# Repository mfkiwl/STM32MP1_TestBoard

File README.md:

### STM32MP1 Embedded Linux breakout board ###

[Bill of materials](STM32MP1_TestBoard/doc/bom/STM32MP1_TestBoard.csv)

[DataSheets](STM32MP1_TestBoard/doc/datasheets)

#### System Overview ####

#### Power Supply ####

#### MPU Power Supply ####

#### MPU DDR ####

#### MicroSD connectors ####

#### USB Connectors ####

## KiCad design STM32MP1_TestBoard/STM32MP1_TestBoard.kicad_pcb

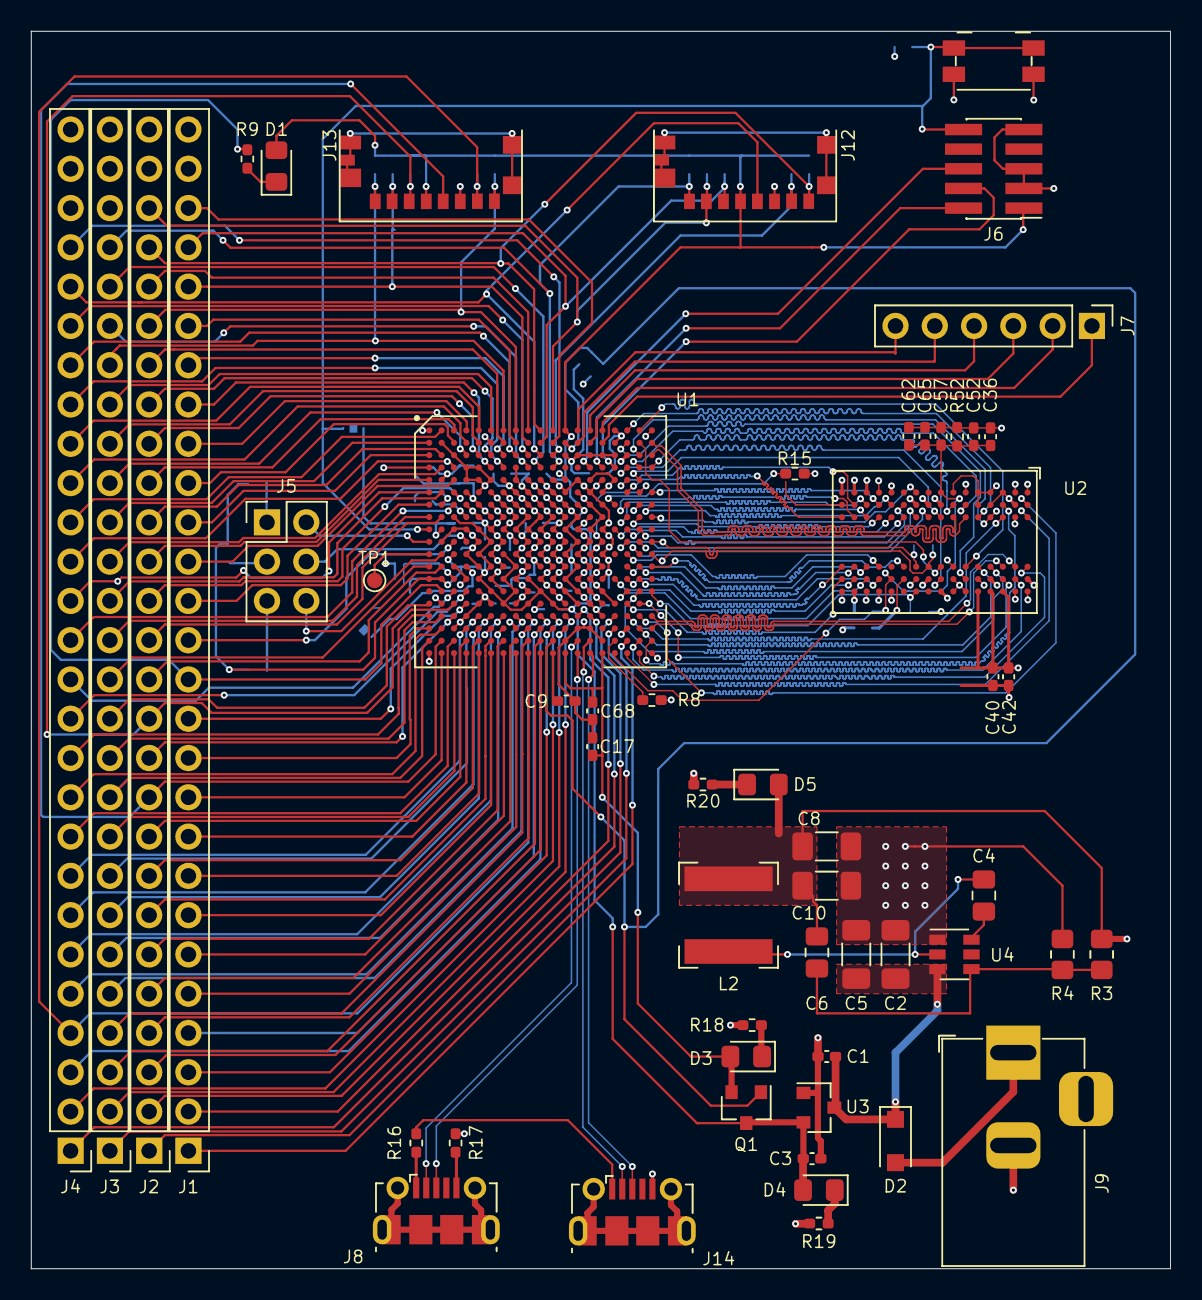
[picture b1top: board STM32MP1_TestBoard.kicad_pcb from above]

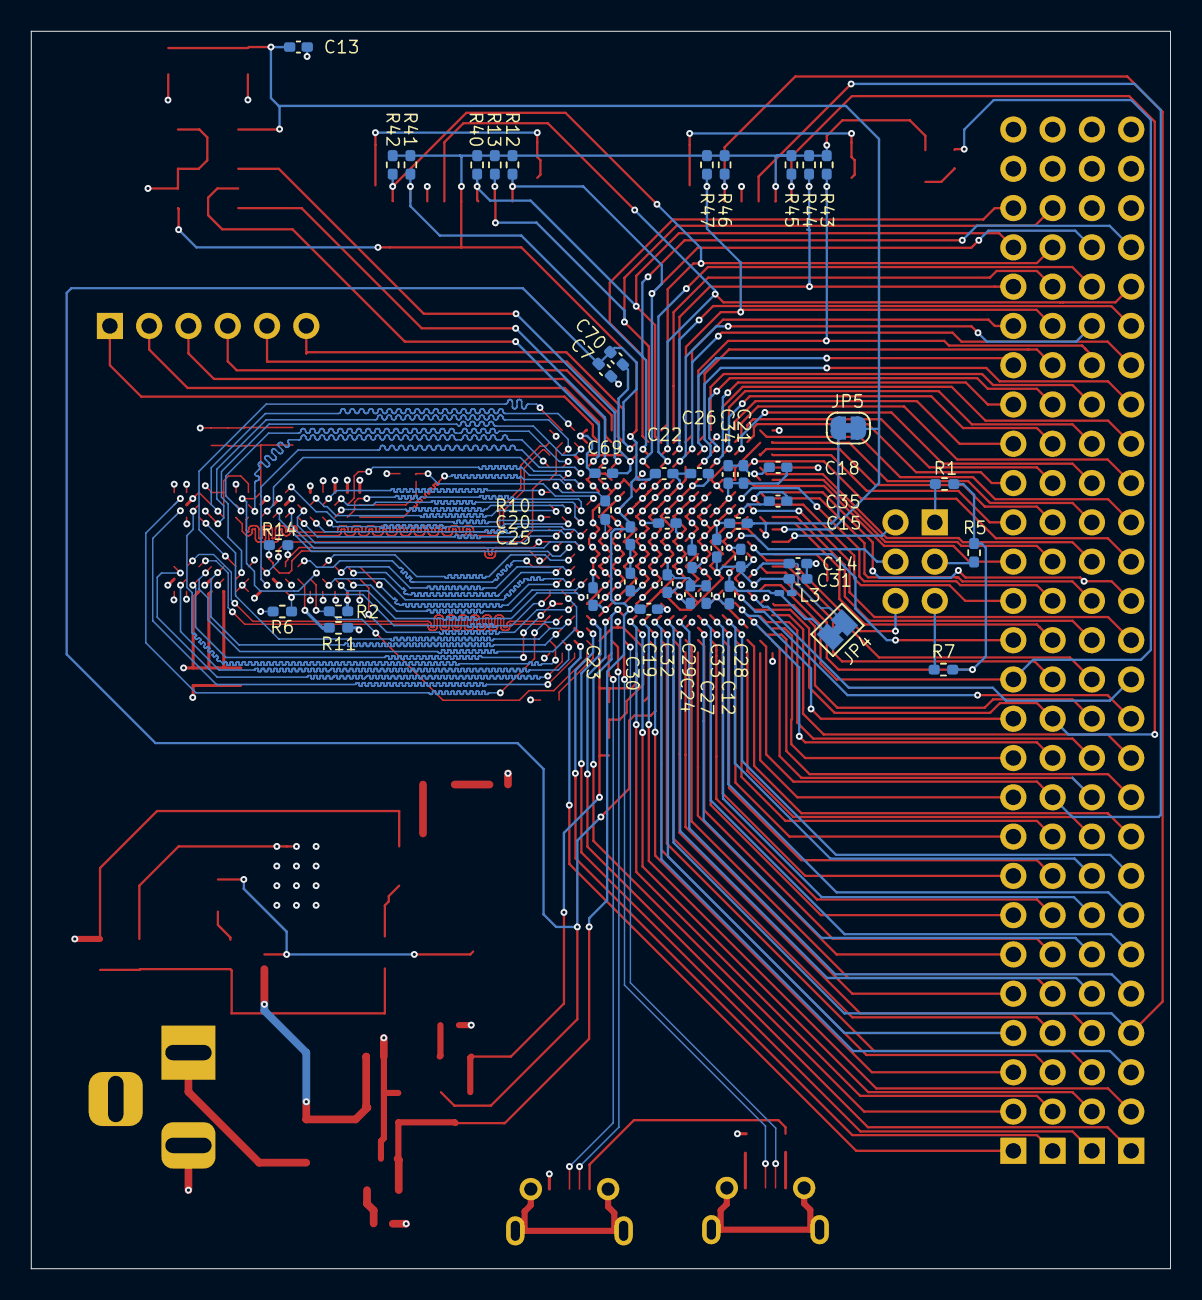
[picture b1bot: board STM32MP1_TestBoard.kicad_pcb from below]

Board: 4 copper layers, 73.7 x 80.0 mm, 100 parts (46 on the bottom side), 195 nets.

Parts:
C1, C12, C14, C17, C18, C19, C20, C21, C22, C23, C24, C25, C26, C27, C28, C29, C30, C31, C32, C33, C34, C35, C68, C70: 1uF; C_0402_1005Metric_Pad0.74x0.62mm_HandSolder
C2, C5, C8, C10: 22uF; C_1206_3216Metric_Pad1.33x1.80mm_HandSolder
C3: 10uF; C_0402_1005Metric_Pad0.74x0.62mm_HandSolder
C4: 100nF; C_0805_2012Metric_Pad1.18x1.45mm_HandSolder
C6: 56pF; C_0805_2012Metric_Pad1.18x1.45mm_HandSolder
C7, C9, C69: 2.2uF; C_0402_1005Metric_Pad0.74x0.62mm_HandSolder
C13, C15: 10nF; C_0402_1005Metric_Pad0.74x0.62mm_HandSolder
C36, C40, C42, C52, C57, C62, C65: 100nF; C_0402_1005Metric_Pad0.74x0.62mm_HandSolder
D1, D3, D4, D5: LED; LED_0805_2012Metric_Pad1.15x1.40mm_HandSolder
D2: D_Schottky; D_SOD-123F
J1, J2, J3, J4: Conn_01x27; PinHeader_1x27_P2.54mm_Vertical
J5: Conn_02x03_Odd_Even; PinHeader_2x03_P2.54mm_Vertical
J6: Conn_02x05_Odd_Even; PinHeader_2x05_P1.27mm_Vertical_SMD
J7: Conn_01x06; PinHeader_1x06_P2.54mm_Vertical
J8, J14: USB_B_Micro; USB_Micro-B_Molex-105017-0001
J9: Barrel_Jack; BarrelJack_Horizontal
J12, J13: Micro_SD_Card; Molex_SDIO_475710001
JP4: Jumper_NC_Small; SolderJumper-2_P1.3mm_Bridged_Pad1.0x1.5mm
JP5: Jumper_NC_Small; SolderJumper-2_P1.3mm_Bridged_RoundedPad1.0x1.5mm
L2: 4.7uH; L_Bourns-SRN6028
L3: LQM18FN4R7M00D; L_0201_0603Metric_Pad0.64x0.40mm_HandSolder
Q1: DMG2302U; SOT-23
R1, R2, R5, R7, R52: 1K; R_0402_1005Metric_Pad0.72x0.64mm_HandSolder
R3: 100K; R_0805_2012Metric_Pad1.20x1.40mm_HandSolder
R4: 82K; R_0805_2012Metric_Pad1.20x1.40mm_HandSolder
R6, R15: 10K; R_0402_1005Metric_Pad0.72x0.64mm_HandSolder
R8: 3K; R_0402_1005Metric_Pad0.72x0.64mm_HandSolder
R9: 680R; R_0402_1005Metric_Pad0.72x0.64mm_HandSolder
R10, R11: 240R; R_0402_1005Metric_Pad0.72x0.64mm_HandSolder
R12, R13, R40, R41, R42, R43, R44, R45, R46, R47: 47K; R_0402_1005Metric_Pad0.72x0.64mm_HandSolder
R14: 100R; R_0402_1005Metric_Pad0.72x0.64mm_HandSolder
R16, R17: 0R; R_0402_1005Metric_Pad0.72x0.64mm_HandSolder
R18, R19, R20: 2K2; R_0402_1005Metric_Pad0.72x0.64mm_HandSolder
SW2: SW_SPST; Panasonic_EVQPUK_EVQPUB
TP1: TestPoint; TestPoint_Pad_D1.0mm
U1: STM32MP157xAB; BGA-361_19x19_16.0x16.0mm
U2: MT41K256M16TW-107; BGA-96_9.0x13.0mm_Layout2x3x16_P0.8mm
U3: SE8233X2; SOT-23
U4: TPS54202DDC; SOT-23-6

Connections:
+5V: J14.1, R16.1
/DDR/DDR_A0: U1.H18, U2.N3
/DDR/DDR_A1: U1.M17, U2.P7
/DDR/DDR_A2: U1.G18, U2.P3
/DDR/DDR_A3: U1.F19, U2.N2
/DDR/DDR_A4: U1.P17, U2.P8
/DDR/DDR_A5: U1.H17, U2.P2
/DDR/DDR_A6: U1.N16, U2.R8
/DDR/DDR_A7: U1.E17, U2.R2
/DDR/DDR_A8: U1.R17, U2.T8
/DDR/DDR_A9: U1.G17, U2.R3
/DDR/DDR_A10: U1.M19, U2.L7
/DDR/DDR_A11: U1.M18, U2.R7
/DDR/DDR_A12: U1.L17, U2.N7
/DDR/DDR_A13: U1.F17, U2.T3
/DDR/DDR_A14: U1.N18, U2.T7
/DDR/DDR_BA0: U1.G19, U2.M2
/DDR/DDR_BA1: U1.N17, U2.N8
/DDR/DDR_BA2: U1.J16, U2.M3
/DDR/DDR_CASN: U1.K17, U2.K3
/DDR/DDR_CKE: R6.1, U1.P19, U2.K9
/DDR/DDR_CLK_N: R14.2, U1.K19, U2.K7
/DDR/DDR_CLK_P: R14.1, U1.L19, U2.J7
/DDR/DDR_CSN: U1.J18, U2.L2
/DDR/DDR_DQ0: U1.A17, U2.E3
/DDR/DDR_DQ1: U1.A18, U2.F7
/DDR/DDR_DQ2: U1.D18, U2.F2
/DDR/DDR_DQ3: U1.B17, U2.F8
/DDR/DDR_DQ4: U1.E18, U2.H3
/DDR/DDR_DQ5: U1.D17, U2.H8
/DDR/DDR_DQ6: U1.D19, U2.G2
/DDR/DDR_DQ7: U1.B18, U2.H7
/DDR/DDR_DQ8: U1.P18, U2.D7
/DDR/DDR_DQ9: U1.T17, U2.C3
/DDR/DDR_DQ10: U1.R18, U2.C8
/DDR/DDR_DQ11: U1.V19, U2.C2
/DDR/DDR_DQ12: U1.W18, U2.A7
/DDR/DDR_DQ13: U1.T18, U2.A2
/DDR/DDR_DQ14: U1.V18, U2.B8
/DDR/DDR_DQ15: U1.W17, U2.A3
/DDR/DDR_DQM0: U1.C18, U2.D3
/DDR/DDR_DQM1: U1.U18, U2.E7
/DDR/DDR_DQS0_N: U1.B19, U2.G3
/DDR/DDR_DQS0_P: U1.C19, U2.F3
/DDR/DDR_DQS1_N: U1.T19, U2.B7
/DDR/DDR_DQS1_P: U1.U19, U2.C7
/DDR/DDR_ODT: U1.H19, U2.K1
/DDR/DDR_RASN: U1.L18, U2.J3
/DDR/DDR_VREF: C36.1, C52.1, C57.1, C62.1, C65.1, R2.2, R52.1, U1.W16, U2.H1, U2.M8
/DDR/DDR_WEN: U1.J17, U2.L3
/DebugInterface1/3.3V_VDD: C3.1, C19.1, C22.1, C25.1, C28.1, C31.1, C33.1, D1.2, D4.2, J6.1, J12.4, J13.4, L3.1, Q1.3, R1.2, R5.2, R7.2, R12.1, R13.1, R40.1, R41.1, R42.1, R43.1, R44.1, R45.1, R46.1, R47.1, U1.A12, U1.G13, U1.H3, U1.J5, U1.K6, U1.L3, U1.L5, U1.L7, U1.M6, U1.M8, U1.N1, U1.N2, U1.N5, U1.N7, U1.N9, U1.P6, U1.P8, U1.P10, U1.R7, U1.R9, U1.R11, U3.2
/DebugInterface1/NRST: C13.1, J6.10, JP5.1, SW2.1, U1.J1
/DebugInterface1/SWCLK: J6.4, U1.D16
/DebugInterface1/SWDIO: J6.2, U1.D15
/DebugInterface1/SWO: J6.6, U1.D14
/GPIO/BOOT_STATUS: J1.13, R9.1, U1.P2
/GPIO/DSI_CK_N: J7.4, U1.A14
/GPIO/DSI_CK_P: J7.3, U1.B14
/GPIO/DSI_D0_N: J7.6, U1.A13
/GPIO/DSI_D0_P: J7.5, U1.B13
/GPIO/DSI_D1_N: J7.2, U1.A15
/GPIO/DSI_D1_P: J7.1, U1.B15
/GPIO/PA0: J2.12, J13.3, R45.2, U1.R3
/GPIO/PA1: J4.8, U1.U4
/GPIO/PA2: J1.10, U1.W2
/GPIO/PA3: J4.13, U1.P3
/GPIO/PA4: J1.12, U1.R4
/GPIO/PA5: J4.12, U1.P4
/GPIO/PA6: J3.8, U1.T5
/GPIO/PA7: J3.7, U1.T6
/GPIO/PA8: J1.22, U1.B8
/GPIO/PA9: J4.21, U1.C8
/GPIO/PA10: J3.1, U1.T16
/GPIO/PA11: J1.1, U1.V17
/GPIO/PA12: J2.1, U1.U16
/GPIO/PA14: J3.12, U1.R1
/GPIO/PA15: J1.21, U1.C7
/GPIO/PB0: J3.9, U1.W3
/GPIO/PB1: J4.9, U1.V3
/GPIO/PB2: J1.2, U1.T13
/GPIO/PB3: J3.21, J13.1, R43.2, U1.A7
/GPIO/PB4: J1.23, J13.2, R44.2, U1.B9
/GPIO/PB5: J4.5, U1.T8
/GPIO/PB6: J2.2, U1.T12
/GPIO/PB7: J3.19, U1.B5
/GPIO/PB8: J1.7, U1.W6
/GPIO/PB9: J3.22, U1.D9
/GPIO/PB10: J1.8, U1.W5
/GPIO/PB11: J3.10, U1.V1
/GPIO/PB12: J2.8, U1.V5
/GPIO/PB13: J4.4, J13.7, R46.2, U1.T9
/GPIO/PB14: J4.22, U1.C9
/GPIO/PB15: J2.22, J13.8, R47.2, U1.A8
/GPIO/PC0: J4.6, U1.T7
/GPIO/PC1: J2.10, J13.5, U1.V2
/GPIO/PC2: J3.11, U1.T2
/GPIO/PC3: J2.11, U1.T3
/GPIO/PC4: J1.9, U1.W4
/GPIO/PC5: J2.9, U1.V4
/GPIO/PC6: J3.23, U1.D10
/GPIO/PC7: J2.23, U1.A9
/GPIO/PC8: J4.24, J12.7, R41.2, U1.C11
/GPIO/PC9: J2.24, J12.8, R42.2, U1.A10
/GPIO/PC10: J3.24, J12.1, R12.2, U1.D11
/GPIO/PC11: J2.25, J12.2, R13.2, U1.A11
/GPIO/PC12: J4.23, J12.5, U1.C10
/GPIO/PC13: J1.14, U1.K3
/GPIO/PC14: J3.14, U1.H1
/GPIO/PC15: J2.14, U1.H2
/GPIO/PD0: J2.18, U1.A3
/GPIO/PD1: J1.19, U1.A4
/GPIO/PD2: J1.24, J12.3, R40.2, U1.B10
/GPIO/PD3: J2.20, U1.C6
/GPIO/PD4: J1.20, U1.D6
/GPIO/PD5: J4.20, U1.D7
/GPIO/PD6: J1.16, U1.E3
/GPIO/PD7: J4.18, U1.B4
/GPIO/PD8: J3.15, U1.F2
/GPIO/PD9: J4.14, U1.G3
/GPIO/PD10: J2.19, U1.C5
/GPIO/PD11: J2.5, U1.V8
/GPIO/PD12: J1.3, U1.U11
/GPIO/PD13: J3.2, U1.U12
/GPIO/PD14: J2.15, U1.F3
/GPIO/PD15: J1.15, U1.G1
/GPIO/PE0: J3.18, U1.C4
/GPIO/PE1: J3.17, U1.B1
/GPIO/PE2: J4.11, U1.T1
/GPIO/PE3: J4.19, U1.A5
/GPIO/PE4: J1.25, U1.B11
/GPIO/PE5: J2.21, U1.B7
/GPIO/PE6: J1.18, U1.B3
/GPIO/PE7: J4.3, U1.T10
/GPIO/PE8: J4.2, U1.T11
/GPIO/PE9: J1.6, U1.W7
/GPIO/PE10: J3.3, U1.V10
/GPIO/PE11: J1.17, U1.C1
/GPIO/PE12: J3.16, U1.D2
/GPIO/PE13: J2.17, U1.C2
/GPIO/PE14: J4.16, U1.D3
/GPIO/PE15: J2.16, U1.E1
/GPIO/PF6: J3.4, U1.V9
/GPIO/PF7: J1.5, U1.W8
/GPIO/PF8: J1.4, U1.U10
/GPIO/PF9: J2.4, U1.W9
/GPIO/PF10: J3.5, U1.U9
/GPIO/PF11: J4.7, U1.U5
/GPIO/PG6: J3.20, U1.A6
/GPIO/PG7: J2.3, U1.W10
/GPIO/PG8: J3.6, U1.U7
/GPIO/PG9: J4.1, U1.T14
/GPIO/PG10: J2.6, U1.V7
/GPIO/PG11: J2.7, U1.V6
/GPIO/PG12: J4.15, U1.F1
/GPIO/PG13: J4.10, U1.U2
/GPIO/PG14: J1.11, U1.U1
/GPIO/PG15: J4.17, U1.A2
/GPIO/PH0: J3.13, U1.M1
/GPIO/PH1: J2.13, U1.M2
/GPIO/USB_Conn/USB_D1_N: J14.3, U1.W14
/GPIO/USB_Conn/USB_D1_P: J14.2, U1.V14
/GPIO/USB_Conn/USB_D2_N: J8.2, U1.V13
/GPIO/USB_Conn/USB_D2_P: J8.3, U1.W13
/PSU/1.35V_VDDCORE: C6.2, C8.1, C10.1, C18.1, C20.1, C21.1, C23.1, C24.1, C26.1, C27.1, C29.1, C30.1, C32.1, C34.1, C35.1, C40.1, C42.1, D5.2, L2.2, R2.1, R3.1, U1.E7, U1.E9, U1.E11, U1.E13, U1.E15, U1.F4, U1.F6, U1.F8, U1.F10, U1.F12, U1.F14, U1.G5, U1.G7, U1.G9, U1.G11, U1.G15, U1.H4, U1.H6, U1.H8, U1.H10, U1.H12, U1.H14, U1.J7, U1.J9, U1.J11, U1.J13, U1.J15, U1.K8, U1.K10, U1.K12, U1.K14, U1.L9, U1.L11, U1.L13, U1.L15, U1.M10, U1.M12, U1.M14, U1.N11, U1.N13, U1.N15, U1.P12, U1.P14, U1.R13, U1.R15, U2.A1, U2.A8, U2.B2, U2.C1, U2.C9, U2.D2, U2.D9, U2.E9, U2.F1, U2.G7, U2.H2, U2.H9, U2.K2, U2.K8, U2.N1, U2.N9, U2.R1, U2.R9
/PSU/1V8_DETECT: C7.1, C70.1, Q1.1, U1.B12, U1.V11
/PSU/3V3_USB: C17.1, C68.1, D3.2, Q1.2, U1.W12, U1.W15
GNDS: C1.2, C2.2, C3.2, C5.2, C7.2, C8.2, C9.1, C10.2, C12.1, C13.2, C14.1, C15.2, C17.2, C18.2, C19.2, C20.2, C21.2, C22.2, C23.2, C24.2, C25.2, C26.2, C27.2, C28.2, C29.2, C30.2, C31.2, C32.2, C33.2, C34.2, C35.2, C36.2, C40.2, C42.2, C52.2, C57.2, C62.2, C65.2, C68.2, J6.3, J6.5, J6.9, J9.2, J12.6, J13.6, J14.5, R4.2, R6.2, R8.1, R10.2, R11.2, R15.2, R17.1, R18.2, R19.2, R20.2, R52.2, SW2.2, U1.A1, U1.A19, U1.B2, U1.B6, U1.C3, U1.C17, U1.D1, U1.D4, U1.D5, U1.D8, U1.E2, U1.E4, U1.E5, U1.E6, U1.E8, U1.E10, U1.E12, U1.E14, U1.E16, U1.F5, U1.F7, U1.F9, U1.F11, U1.F13, U1.F15, U1.G2, U1.G4, U1.G6, U1.G8, U1.G10, U1.G12, U1.G14, U1.H5, U1.H7, U1.H9, U1.H11, U1.H13, U1.H15, U1.J3, U1.J4, U1.J6, U1.J8, U1.J10, U1.J12, U1.J14, U1.K2, U1.K5, U1.K7, U1.K9, U1.K11, U1.K13, U1.K15, U1.L4, U1.L6, U1.L8, U1.L10, U1.L12, U1.L14, U1.M3, U1.M5, U1.M7, U1.M9, U1.M11, U1.M13, U1.M15, U1.N4, U1.N6, U1.N8, U1.N10, U1.N12, U1.N14, U1.P5, U1.P7, U1.P9, U1.P11, U1.P13, U1.P15, U1.R2, U1.R5, U1.R6, U1.R8, U1.R10, U1.R12, U1.R14, U1.R16, U1.T4, U1.T15, U1.U3, U1.U6, U1.U8, U1.U13, U1.U14, U1.U17, U1.V12, U1.V15, U1.W1, U1.W19, U2.A9, U2.B1, U2.B3, U2.B9, U2.D1, U2.D8, U2.E1, U2.E2, U2.E8, U2.F9, U2.G1, U2.G8, U2.G9, U2.J2, U2.J8, U2.M1, U2.M9, U2.P1, U2.P9, U2.T1, U2.T9, U3.1, U4.1
unnamed: C1.1, C2.1, C5.1, D2.1, U3.3, U4.3
unnamed: C4.1, L2.1, U4.2
unnamed: C4.2, U4.6
unnamed: C6.1, R3.2, R4.1, U4.4
unnamed: C9.2, U1.W11
unnamed: C12.2, JP4.2, L3.2, U1.M4
unnamed: C14.2, JP4.1, U1.N3
unnamed: C15.1, JP5.2, U1.J2
unnamed: C69.1, C70.2, U1.C12, U1.C13, U1.C14, U1.C15, U1.C16
unnamed: C69.2, U1.A16, U1.B16
unnamed: D1.1, R9.2
unnamed: D2.2, J9.1
unnamed: D3.1, R18.1
unnamed: D4.1, R19.1
unnamed: D5.1, R20.1
unnamed: J5.1, R1.1
unnamed: J5.2, U1.K1
unnamed: J5.3, R5.1
unnamed: J5.4, U1.K4
unnamed: J5.5, R7.1
unnamed: J5.6, U1.L2
unnamed: J8.1, R16.2
unnamed: J8.5, R17.2
unnamed: R8.2, U1.V16
unnamed: R10.1, U1.F18
unnamed: R11.1, U2.L8
unnamed: R15.1, U1.G16, U2.T2
unnamed: TP1.1, U1.L1

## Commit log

2020-11-14 First draft schema
2020-11-14 updated bom, readme
2020-11-15 swapped smps for ldo
2020-11-15 minor schema updates
2020-11-16 updated netlist
2020-11-16 updated schematic design
2020-11-18 layout update
    backup. work in progress
2020-11-20 updated to use stm32MP15x symbol library
2020-11-30 added traces for sdio, dsi and swd connectors
2020-12-02 added psu
2020-12-05 swapped DDR3 high/low strobe diff pairs
    - corrected DRC errors
2020-12-06 finished RevA draft layout
    - Added MPU bypass caps
    - length tuned DDR3L traces
2020-12-07 updated RevA draft
    - Added outer layer ground planes
    - Added outer layer keepout zones for DDR3 area
2020-12-07 updated RevA draft
    - added silkscreen
2020-12-08 RevA layout final
2020-12-10 added ibom
2021-01-01 updated schematic
    changed STM32MP157xAB to STM32MP157xAC
2021-01-01 updated schema and bom docs
2021-01-01 updated schema svg and readme
2021-01-01 added layout render to readme
2021-01-10 corrected STM32MP157 footprint
2021-01-14 Auto stash before merge of "main" and "origin/main"
2021-01-26 added USART tags to GPIO pins on schema
